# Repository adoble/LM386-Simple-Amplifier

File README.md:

# LM386 Based Audio Stereo Amplifier

This is a simple LM386 based audio amplifier that I can use as a utility amplifier when dealing with audio signals. It is not really a "hifi" amplifier, but produces an acceptable sound on small loudspeakers.

The main purpose of the project though, was to do a [perfboard](https://en.wikipedia.org/wiki/Perfboard) design using [KiCad](https://kicad-pcb.org/). I've usually done the layout design in the past either with paper and pencil or even on the fly directly on the board. The results have not  been good.

## Circuit
The circuit is based strongly on the design shown in [Circuit Basics](https://www.circuitbasics.com/build-a-great-sounding-audio-amplifier-with-bass-boost-from-the-lm386/).

## Layout

One of the main reasons for this project was to see if KiCad could be used to layout the wiring on a perfboard, i.e. soldering bare wires on the back side of the perfboard. The result is shown below:

I set the grid to 2.54mm and then laid out the footprints. I then routed the pins together making sure that each track had only 90 degree turns. Finally I used to array layout function in KiCad to layout the vias. These represent the holes on the perfboard.  

I tried to get all components on the front side of the board with the connections as bare wires on the back side. Unfortunately I made a couple of changes after I had soldered some of the components and wiring, meaning a planar layout I had achieved before was no longer possible. You can see that with the one red (front side) track on the layout. I used an insulated wire, again on the back side, but put some isolation tape between it and the bare wires just to be sure.

Using the KiCad PCB tool meant it was a lot easier to do a clean(er) layout than when I used paper and pencil.

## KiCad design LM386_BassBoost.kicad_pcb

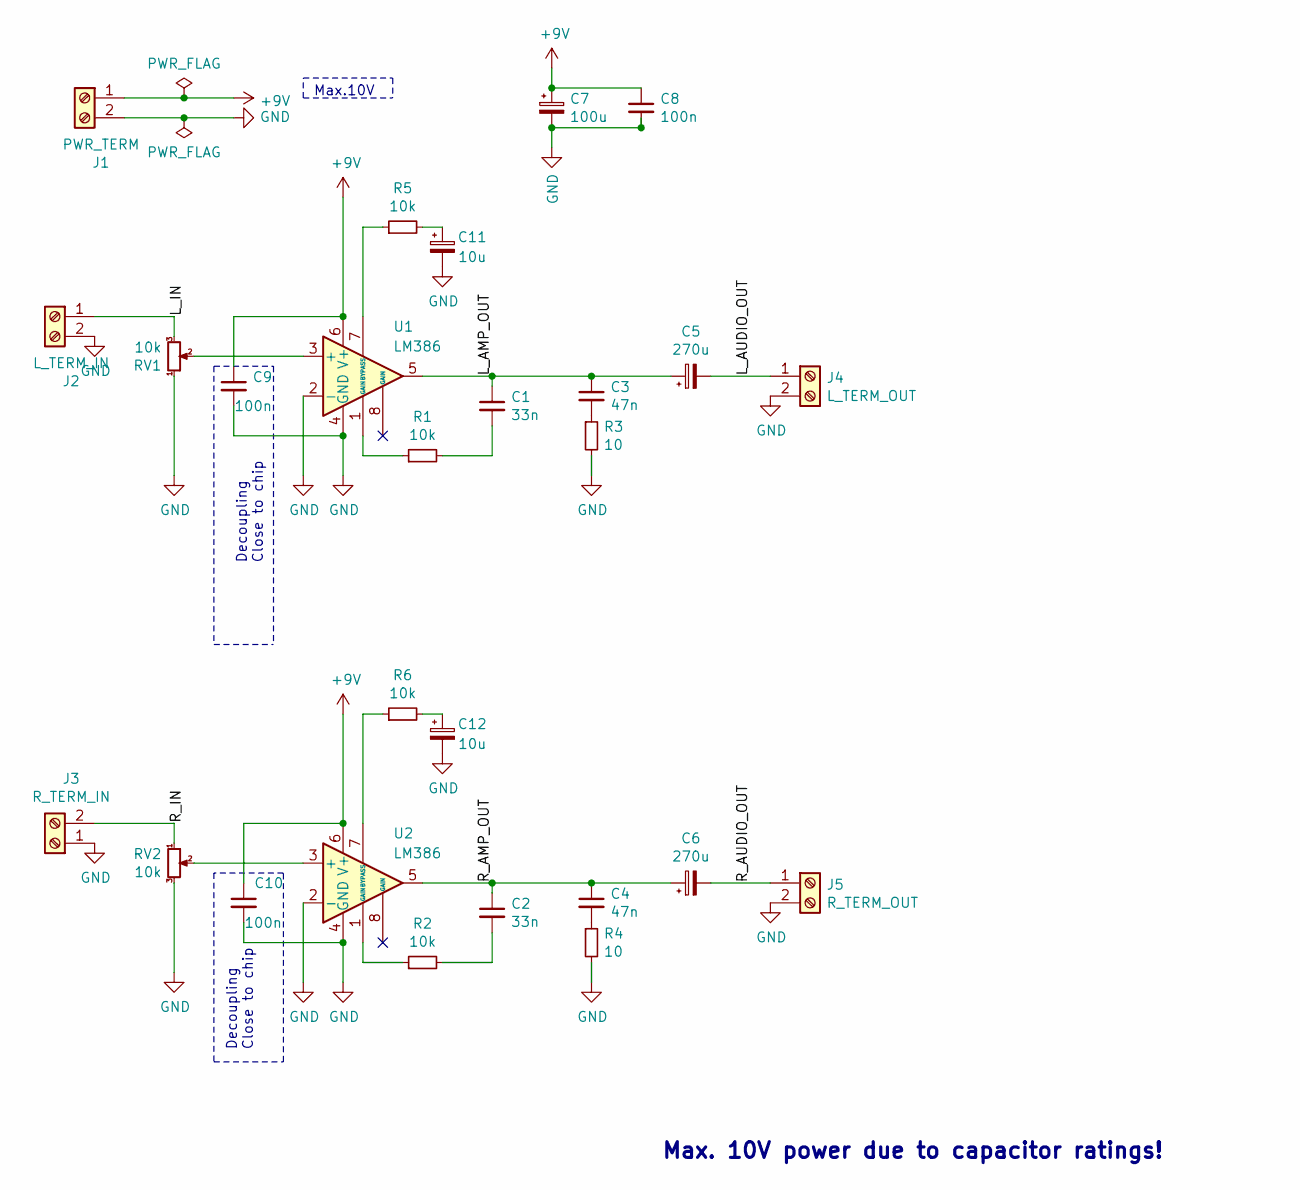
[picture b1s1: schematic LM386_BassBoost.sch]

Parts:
C1, C2: 33n; C_Disc_D7.0mm_W2.5mm_P5.00mm
C3, C4: 47n; C_Disc_D7.0mm_W2.5mm_P5.00mm
C5, C6: 270u; CP_Radial_D6.3mm_P2.50mm
C7: 100u; CP_Radial_D6.3mm_P2.50mm
C8: 100n; C_Disc_D3.0mm_W1.6mm_P2.50mm
C9, C10: 100n; C_Disc_D7.0mm_W2.5mm_P5.00mm
C11, C12: 10u; CP_Radial_D5.0mm_P2.50mm
J1: PWR_TERM; Screw_Terminal_1x02
J2: L_TERM_IN; Screw_Terminal_1x02
J3: R_TERM_IN; Screw_Terminal_1x02
J4: L_TERM_OUT; Screw_Terminal_1x02
J5: R_TERM_OUT; Screw_Terminal_1x02
R1, R2, R5, R6: 10k; R_Axial_DIN0207_L6.3mm_D2.5mm_P10.16mm_Horizontal
R3, R4: 10; R_Axial_DIN0207_L6.3mm_D2.5mm_P10.16mm_Horizontal
RV1, RV2: 10k; Potentiometer_Trimmer_Bourns_3310Y
U1, U2: LM386; DIP-8_W7.62mm

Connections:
+9V: C7.1, C8.1, C9.1, C10.1, J1.1, U1.6 (V+), U2.6 (V+)
/L_AMP_OUT: C1.1, C3.1, C5.1, U1.5
/L_AUDIO_OUT: C5.2, J4.1
/R_AMP_OUT: C2.1, C4.1, C6.1, U2.5
/R_AUDIO_OUT: C6.2, J5.1
GND: C7.2, C8.2, C9.2, C10.2, C11.2, C12.2, J1.2, J2.2, J3.1, J4.2, J5.2, R3.2, R4.2, RV1.1, RV2.3, U1.2 (-), U1.4 (GND), U2.2 (-), U2.4 (GND)
unnamed: C1.2, R1.2
unnamed: C2.2, R2.2
unnamed: C3.2, R3.1
unnamed: C4.2, R4.1
unnamed: C11.1, R5.2
unnamed: C12.1, R6.2
unnamed: J2.1, RV1.3
unnamed: J3.2, RV2.1
unnamed: R1.1, U1.1 (GAIN)
unnamed: R2.1, U2.1 (GAIN)
unnamed: R5.1, U1.7 (BYPASS)
unnamed: R6.1, U2.7 (BYPASS)
unnamed: RV1.2, U1.3 (+)
unnamed: RV2.2, U2.3 (+)

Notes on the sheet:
Max.10V
Max. 10V power due to capacitor ratings!
Decoupling Close to chip

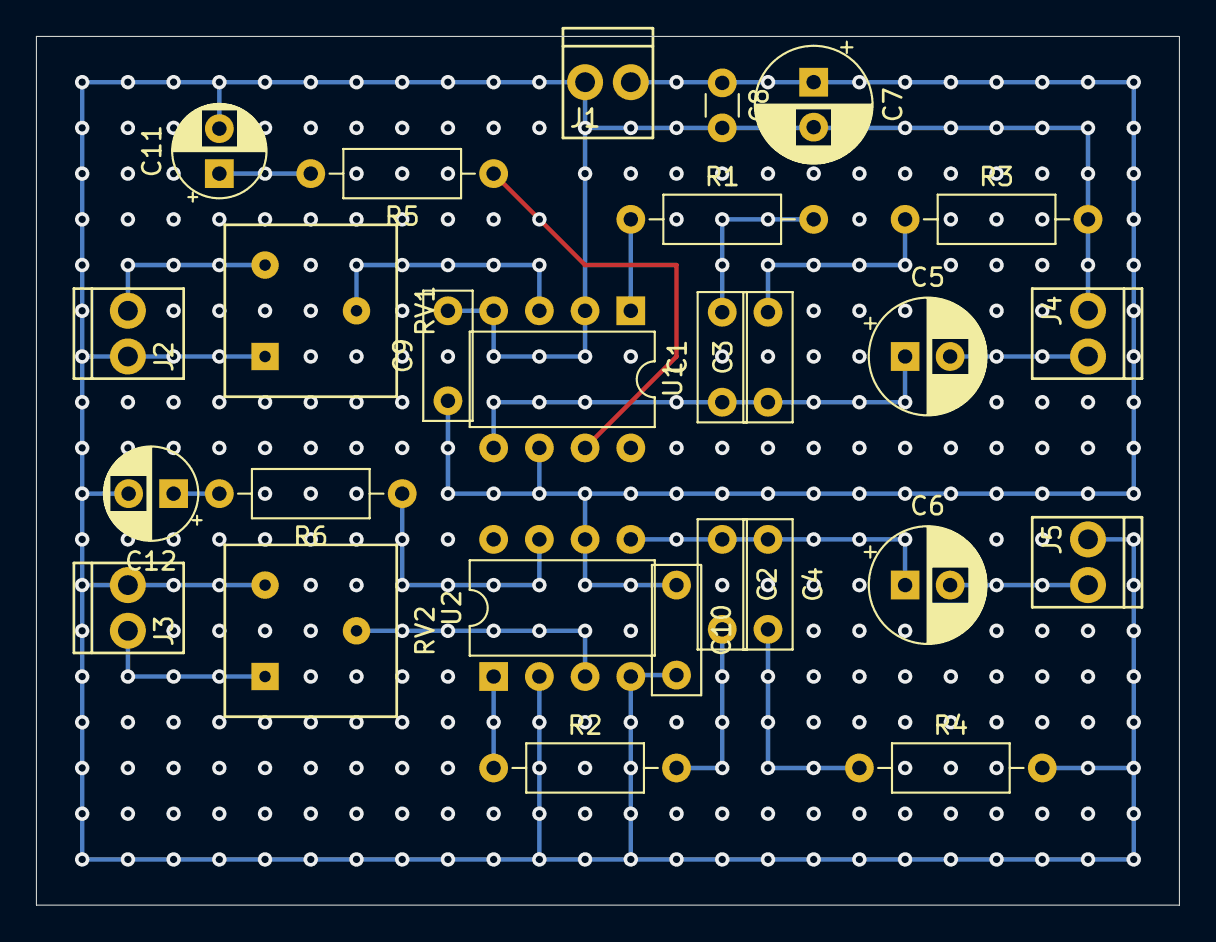
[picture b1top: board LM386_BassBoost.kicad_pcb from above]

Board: 2 copper layers, 63.5 x 48.3 mm, 27 parts (0 on the bottom side), 20 nets.

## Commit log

2020-09-14 Initial version
2020-09-14 Link to perfboard
